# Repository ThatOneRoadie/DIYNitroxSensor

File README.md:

# Notes as of February 8, 2025
Read the readme below carefully as ***this project repo is not complete*** and will not result in a working product if used (yet). I've sent boards off to everyone's favorite PCB fab to be printed, and have yet to edit the models to accommodate the added sensor. The code does work and appears to be stable in "contaminated air" (read: car exhaust) testing. The Oxygen sensor portion was confirmed as accurate against a known-good sensor at my local dive shop.

# DIYNitroxSensor
This is a fork of @rolandoman's fantastic Kitable Nitrox sensor, to add a CO Alarm in the event of contaminated air supply. Given recent dive incidents, a CO Sensor add-in for about $15 (Cheaper than the O2 Sensors too) seems prudent.
Having this kitable for remote sites (bring spare sensors/parts, easy), and keep the project budget low, are the primary goals. Ideally, this entire analyzer would be sub-$50 (USD) completed.

# This is LIFE SUPPORT EQUIPMENT.
As always, once your project is complete, I would ***highly recommend*** you test your sensor against a known-good sensor, e.g. at a local dive store or nitrox fill site with a known-good analyzer. Verify everything works; _your life depends on it_. Analyze your cylinder with more than one sensor, and don't fall victim to confirmation bias (I'm expecting EAN32, my DIY sensor reads 32, perfect let's go diving). Do not dive Enriched Air Nitrox without first taking a course with your local certifying agency regarding the dangers and analysis processes.

# Sources and other information
This project borrows heavily on https://www.divetech.com/post/the-20-nitrox-analyzer (Link is now dead, I'm e-mailing the DiveTech Employee who previously wrote that article), but adds a number of improvements including rechargeable battery circuit, custom PCB, and stronger case.

This repository will mostly contain arduino code files and KiCAD files, plus edits to rolandoman's STL files to house the CO Sensor and slightly different sized PCB.

Rolandoman's main project page for the analyzer **without the CO sensor** can be found on instructables: https://www.instructables.com/Yet-Another-DIY-Nitrox-Sensor/

Rolandoman's 3D printer files, again **without the CO Sensor** can be found on Thingiverse: https://www.thingiverse.com/thing:6300317

This is a diagram of the basic connections for the arduino pro mini below, including the CO Sensor on ADC Pin A2 (only a single pin is needed for the ZE15-CO Package):

Here is a picture of the specialized PCB for the project designed on KiCAD. File included in the project.

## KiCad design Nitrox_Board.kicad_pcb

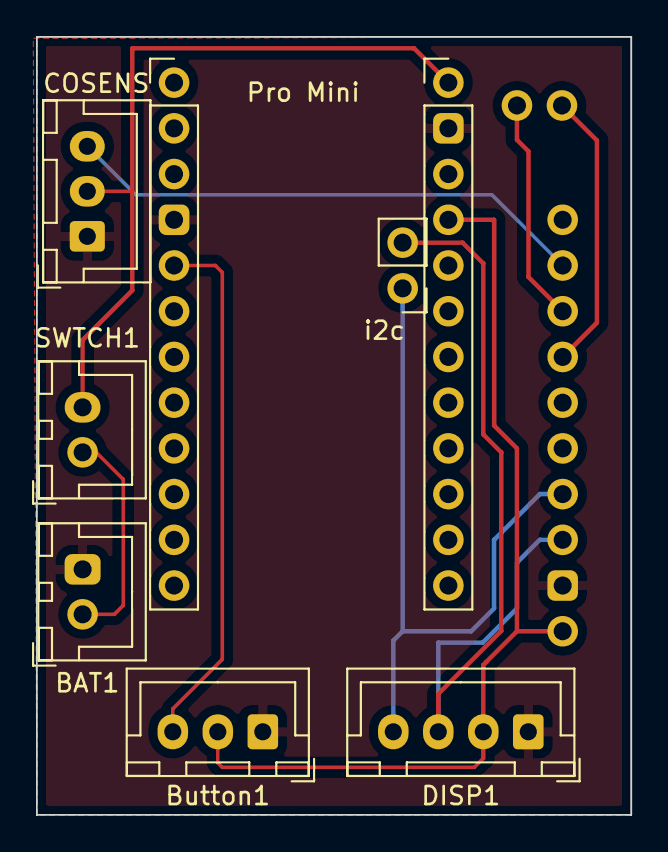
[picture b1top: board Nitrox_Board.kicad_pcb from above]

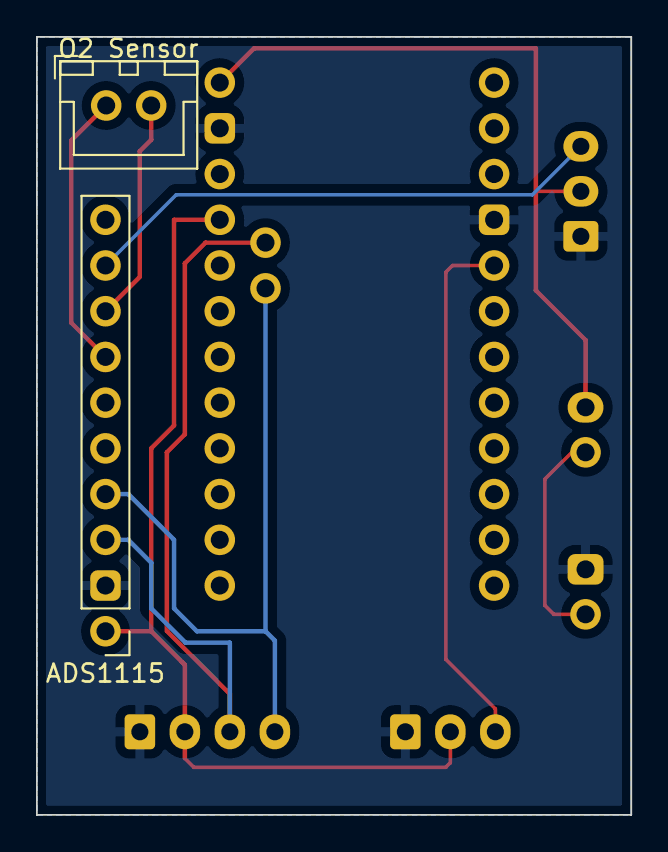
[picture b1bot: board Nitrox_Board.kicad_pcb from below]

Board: 2 copper layers, 33.0 x 43.2 mm, 10 parts (2 on the bottom side), 9 nets.

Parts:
ADS1115: PinHeader_1x10_P2.54mm_Vertical
BAT1: JST_XH_B2B-XH-A_1x02_P2.50mm_Vertical
Button1: JST_XH_B3B-XH-A_1x03_P2.50mm_Vertical
COSENS: JST_XH_B3B-XH-A_1x03_P2.50mm_Vertical
DISP1: JST_XH_B4B-XH-A_1x04_P2.50mm_Vertical
O2 Sensor: JST_XH_B2B-XH-A_1x02_P2.50mm_Vertical
Pro Mini: PinHeader_1x12_P2.54mm_Vertical
ProMini2: PinHeader_1x12_P2.54mm_Vertical
SWTCH1: JST_XH_B2B-XH-A_1x02_P2.50mm_Vertical
i2c: PinHeader_1x02_P2.54mm_Vertical

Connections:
GND: ADS1115.2, BAT1.2, Button1.1, COSENS.1, DISP1.1, Pro Mini.4, ProMini2.2
unnamed: ADS1115.7, O2 Sensor.1
unnamed: ADS1115.8, O2 Sensor.2
unnamed: BAT1.1, SWTCH1.1
unnamed: Button1.3, Pro Mini.5
unnamed: COSENS.2, ProMini2.1, SWTCH1.2
SCL: ADS1115.3, DISP1.3, i2c.2
SDA: ADS1115.4, DISP1.4, i2c.1
VCC: ADS1115.1, Button1.2, DISP1.2, ProMini2.4

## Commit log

2023-11-07 Update README.md
    Initial description
2023-11-07 Create diy_o2_analyzer.ino
    First upload
2023-11-08 Delete diy_o2_analyzer.ino
    Old copy
2023-11-08 Update README.md
    update
2023-11-08 Update README.md
    sdf
2023-11-08 Update README.md
    asd
2023-11-08 Update README.md
    dfg
2023-11-08 Update README.md
    sf
2023-11-08 Update README.md
    img
2023-11-08 Update README.md
    PCB imgs
2023-11-09 Create Test
    tset
2023-11-09 Delete GerberFiles/Test
    deleted
2023-11-12 Update README.md
    link
2023-11-12 Update README.md
    linky
2023-11-12 Update README.md
    dgfh
2023-11-12 Update README.md
    tyh
2025-01-24 Initial Sketch
    Pending some breadboard work, basic diagram and pinouts.
2025-01-26 CO Sensor Changes
    Add CO Sensor Alarm to display render, add CO Sensor to ADC pin 3 (non-diff reading), Add various math/variables for CO Sensor and to differentiate from O2 Sensor, Always calibrate on Boot/Reset, and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
    PCB Updated to add CO Sensor leads and LED lead for button illumination when on.
2025-01-26 Delete Nitrox_Board.kicad_prl
    Junk Files
2025-01-26 Delete Nitrox_Board.kicad_pro
    Junk Files
2025-01-26 Update pinouts and readme
    Updated Pinouts per Mfg diagram for ZE15-CO and updated readme.
2025-02-08 V1.0 PCB iteration
    Final changes to board for CO Sensor after wiring test, send Gerber and drill files to PCBWay.
2025-02-08 Board Thickness
    Loljk board thickness, now we're final.
2025-02-08 Update README.md
    Current progress (PCB off to fab), notes.
